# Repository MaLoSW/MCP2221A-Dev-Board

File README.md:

# MCP2221A-Dev-Board
Project for a USB to I2C/ART combo using a MCP2221A chip

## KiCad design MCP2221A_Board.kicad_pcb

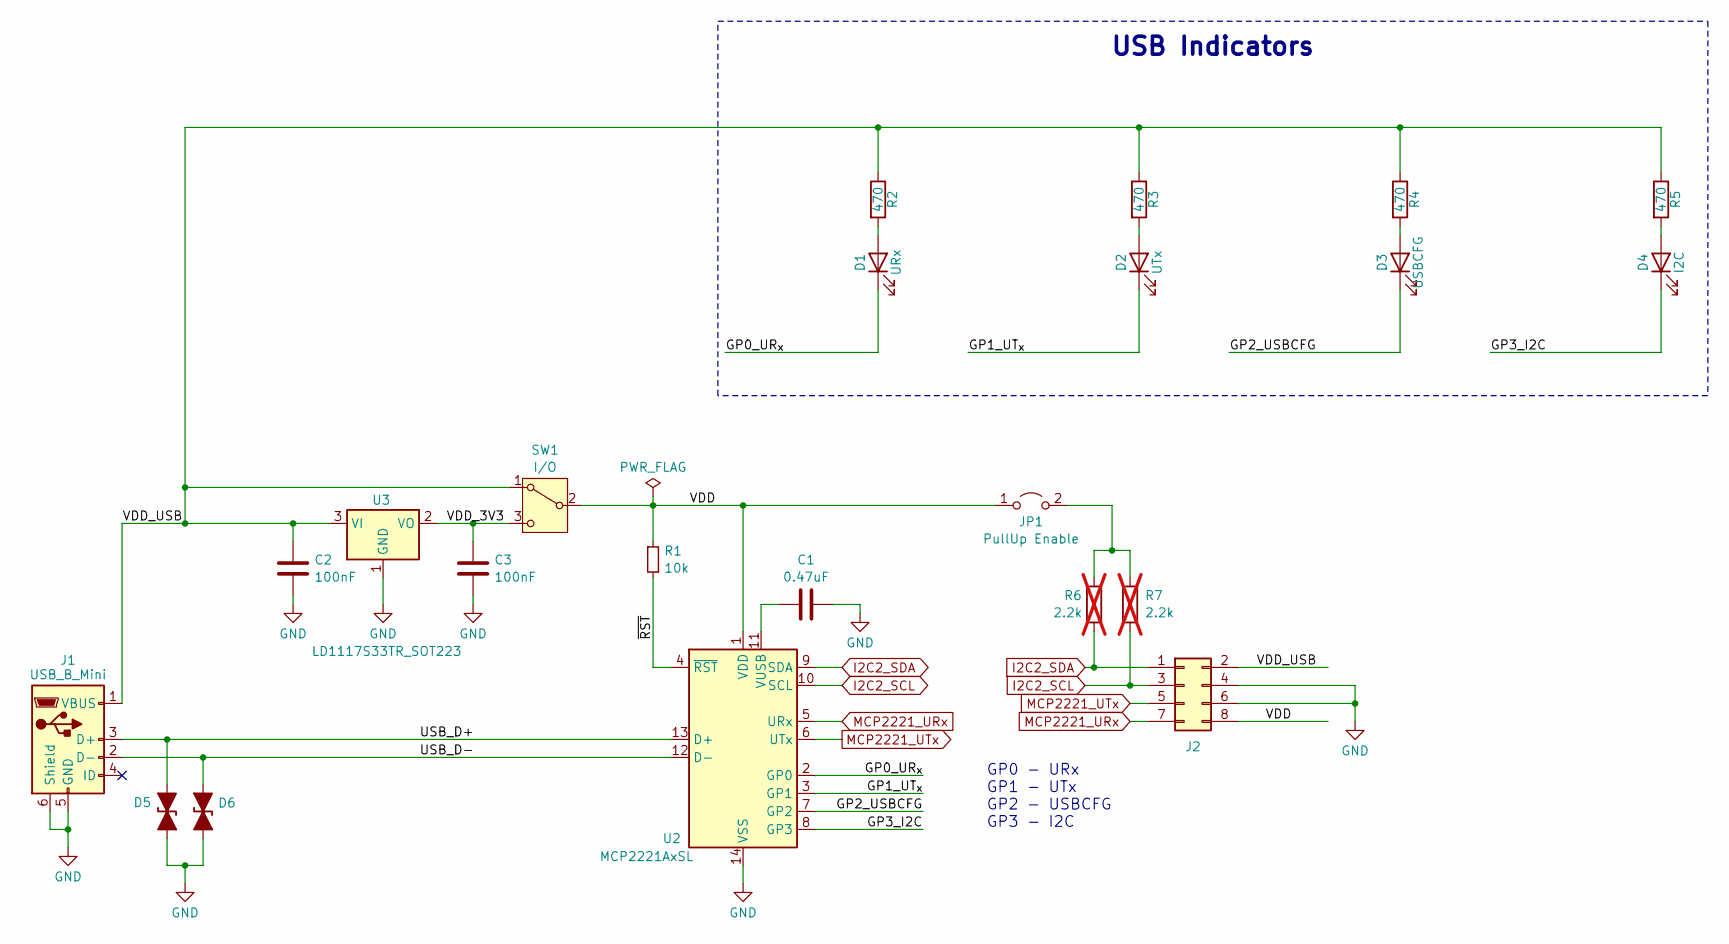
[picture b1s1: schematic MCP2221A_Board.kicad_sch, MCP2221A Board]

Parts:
C1: 0.47uF; C_0805_2012Metric_Pad1.18x1.45mm_HandSolder
C2, C3: 100nF; C_0805_2012Metric_Pad1.15x1.40mm_HandSolder
D1: URx; LED_0805_2012Metric_Pad1.15x1.40mm_HandSolder
D2: UTx; LED_0805_2012Metric_Pad1.15x1.40mm_HandSolder
D3: USBCFG; LED_0805_2012Metric_Pad1.15x1.40mm_HandSolder
D4: I2C; LED_0805_2012Metric_Pad1.15x1.40mm_HandSolder
D5, D6: PGB1010603; D_0603_1608Metric_TVS
J1: USB_B_Mini; USB_Mini-B_Wuerth_65100516121_Horizontal
J2: Conn_02x04_Odd_Even; PinHeader_2x04_P2.54mm_Vertical
JP1: PullUp Enable; PinHeader_1x02_P2.54mm_Vertical
R1: 10k; R_0805_2012Metric_Pad1.20x1.40mm_HandSolder
R2, R3, R4, R5: 470; R_0805_2012Metric_Pad1.20x1.40mm_HandSolder
R6, R7: 2.2k; R_0805_2012Metric_Pad1.20x1.40mm_HandSolder; not fitted
SW1: I/O; PinHeader_1x03_P2.54mm_Vertical
U2: MCP2221AxSL; SOIC-14_3.9x8.7mm_P1.27mm
U3: LD1117S33TR_SOT223; SOT-223-3_TabPin2

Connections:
/GP0_UR_{x}: D1.1 (K), U2.2 (GP0)
/GP1_UT_{x}: D2.1 (K), U2.3 (GP1)
/GP2_USBCFG: D3.1 (K), U2.7 (GP2)
/GP3_I2C: D4.1 (K), U2.8 (GP3)
/USB_D+: D5.2 (A2), J1.3 (D+), U2.13 (D+)
/USB_D-: D6.2 (A2), J1.2 (D-), U2.12 (D-)
/VDD: J2.8, JP1.1 (A), R1.1, SW1.2 (B), U2.1 (VDD)
/VDD_3V3: C3.1, SW1.3 (C), U3.2 (VO)
/VDD_USB: C2.1, J1.1 (VBUS), J2.2, R2.1, R3.1, R4.1, R5.1, SW1.1 (A), U3.3 (VI)
/~RST: R1.2, U2.4 (~RST)
GND: C1.2, C2.2, C3.2, D5.1 (A1), D6.1 (A1), J1.5 (GND), J1.6 (Shield), J2.4, J2.6, U2.14 (VSS), U3.1 (GND)
I2C2_SCL: J2.3, R7.2, U2.10 (SCL)
I2C2_SDA: J2.1, R6.2, U2.9 (SDA)
MCP2221_URx: J2.7, U2.5 (URx)
MCP2221_UTx: J2.5, U2.6 (UTx)
unnamed: D1.2 (A), R2.2
unnamed: D2.2 (A), R3.2
unnamed: D3.2 (A), R4.2
unnamed: D4.2 (A), R5.2
unnamed: JP1.2 (B), R6.1, R7.1
unnamed: C1.1, U2.11 (VUSB)

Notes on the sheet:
USB Indicators
GP0 - URx GP1 - UTx GP2 - USBCFG GP3 - I2C

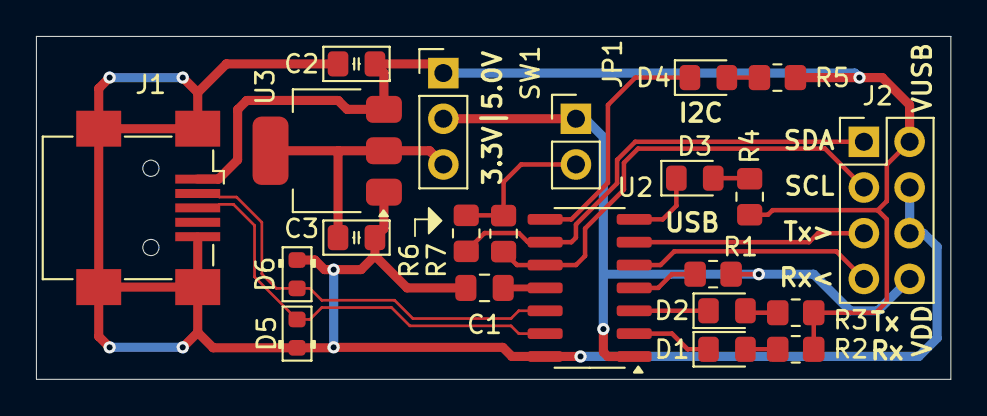
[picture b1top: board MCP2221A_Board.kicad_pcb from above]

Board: 2 copper layers, 50.8 x 19.0 mm, 22 parts (0 on the bottom side), 21 nets.

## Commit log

2024-08-31 Initial PCB already sent to manufacturer
2024-08-31 Updated VDD track width and documentation
    - Added 3D view
    - Added Interactive BOM
2024-09-18 Updated documentation
